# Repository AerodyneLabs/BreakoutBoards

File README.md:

BreakoutBoards
==============

Miscellaneous breakout boards

8 pin SOIC/SSOP | 
[Order](http://oshpark.com/shared_projects/tNmsyAuE) - 
[Gerbers](https://github.com/AerodyneLabs/BreakoutBoards/raw/master/8p-BoB/8p-BoB-Gerber.zip)

SOT23/SOT223/SC70 | 
[Order](http://oshpark.com/shared_projects/5Zmb9JxP) - 
[Gerbers](https://github.com/AerodyneLabs/BreakoutBoards/raw/master/SOT-BoB/SOT-BoB-Gerber.zip)

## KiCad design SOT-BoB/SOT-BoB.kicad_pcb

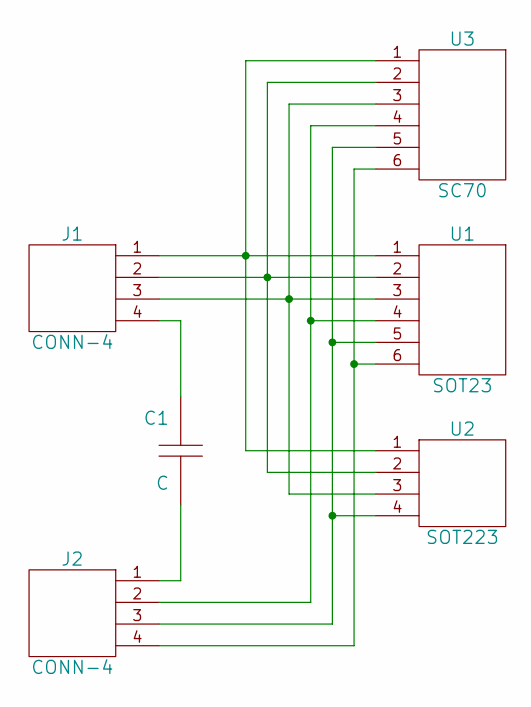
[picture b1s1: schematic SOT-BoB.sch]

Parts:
C1: C; Voltage V
J1, J2: CONN-4
U1: SOT23
U2: SOT223
U3: SC70

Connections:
unnamed: J2.3, U1.5, U2.4, U3.5
unnamed: J2.4, U1.6, U3.6
unnamed: C1.1, J1.4
unnamed: C1.2, J2.1
unnamed: J2.2, U1.4, U3.4
unnamed: J1.1, U1.1, U2.1, U3.1
unnamed: J1.2, U1.2, U2.2, U3.2
unnamed: J1.3, U1.3, U2.3, U3.3

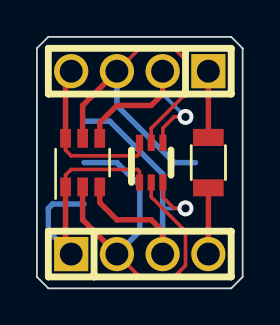
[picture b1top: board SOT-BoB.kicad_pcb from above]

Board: 2 copper layers, 11.4 x 14.0 mm, 6 parts (1 on the bottom side), 8 nets.

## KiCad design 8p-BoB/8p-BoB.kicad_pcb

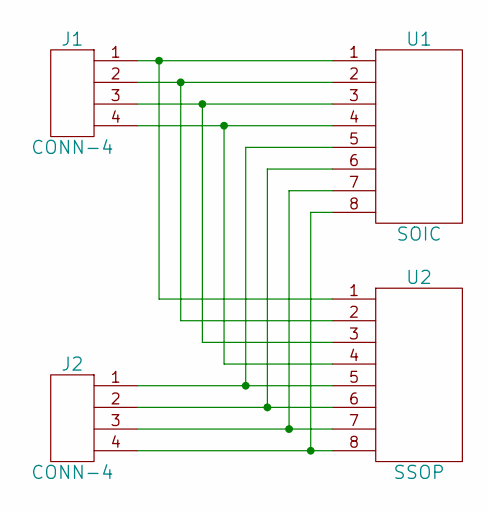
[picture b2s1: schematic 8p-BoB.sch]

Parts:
J1, J2: CONN-4
U1: SOIC
U2: SSOP

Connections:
unnamed: J2.2, U1.6, U2.6
unnamed: J2.1, U1.5, U2.5
unnamed: J1.4, U1.4, U2.4
unnamed: J1.3, U1.3, U2.3
unnamed: J1.2, U1.2, U2.2
unnamed: J1.1, U1.1, U2.1
unnamed: J2.4, U1.8, U2.8
unnamed: J2.3, U1.7, U2.7

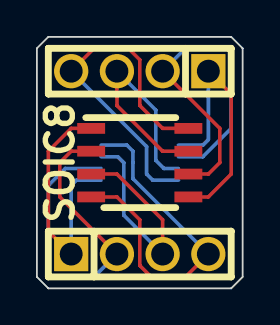
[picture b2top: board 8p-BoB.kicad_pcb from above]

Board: 2 copper layers, 11.4 x 14.0 mm, 4 parts (1 on the bottom side), 8 nets.

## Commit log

2013-10-30 Add 8 pin SOIC/SSOP breakout board
2013-10-30 Add 8 pin SOIC/SSOP OSHPark link
2013-10-30 Update README.md
    Fix my oopsie
2013-10-30 Update 8p-BoB to new conn-4 symbol
2013-10-30 Add SOT breakout board
2013-10-30 Change format of readme
2013-10-30 Fix typo
